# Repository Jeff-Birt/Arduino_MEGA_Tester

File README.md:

# Arduino_MEGA_Tester
This project started out as a way to learn about vintage DRAM chips by building an Arduino based tester. Yes, similar projects exist but part of the fun comes from learning to do it yourself.

After getting the testing of 4164 and 41256 DRAMs working someone asked about testing 4116 DRAMs which require three supply voltages and have the nasty tendency to short the rails together when they fail. This required adding some TVS diode arrays to clamp the I/O to 5V/GND and using some small encapsulated DC-DC converters also made sense.

I started with an Arduino Mega as I had one handy, adn also ported it to the Uno, Micro, and Nano. I designed a PCB around the Micro as well. After using the Mega to build an RCA 1802 tester it ocurred to me that by going back to the Mega with its numerous I/O and larger code space, that I could build a more universal tester.

So, after a 6 month hiatus on the project I picked it up again, moved back to the Mega 2560 and designed a 'Mega Tester' shield for it. The shield accepts 'PODs' which is a daughter board customized for a particular range of ICs. For example the 'DRAM Tester POD' which is for 4116, 4164, 41256 and 41464 DRAMs.

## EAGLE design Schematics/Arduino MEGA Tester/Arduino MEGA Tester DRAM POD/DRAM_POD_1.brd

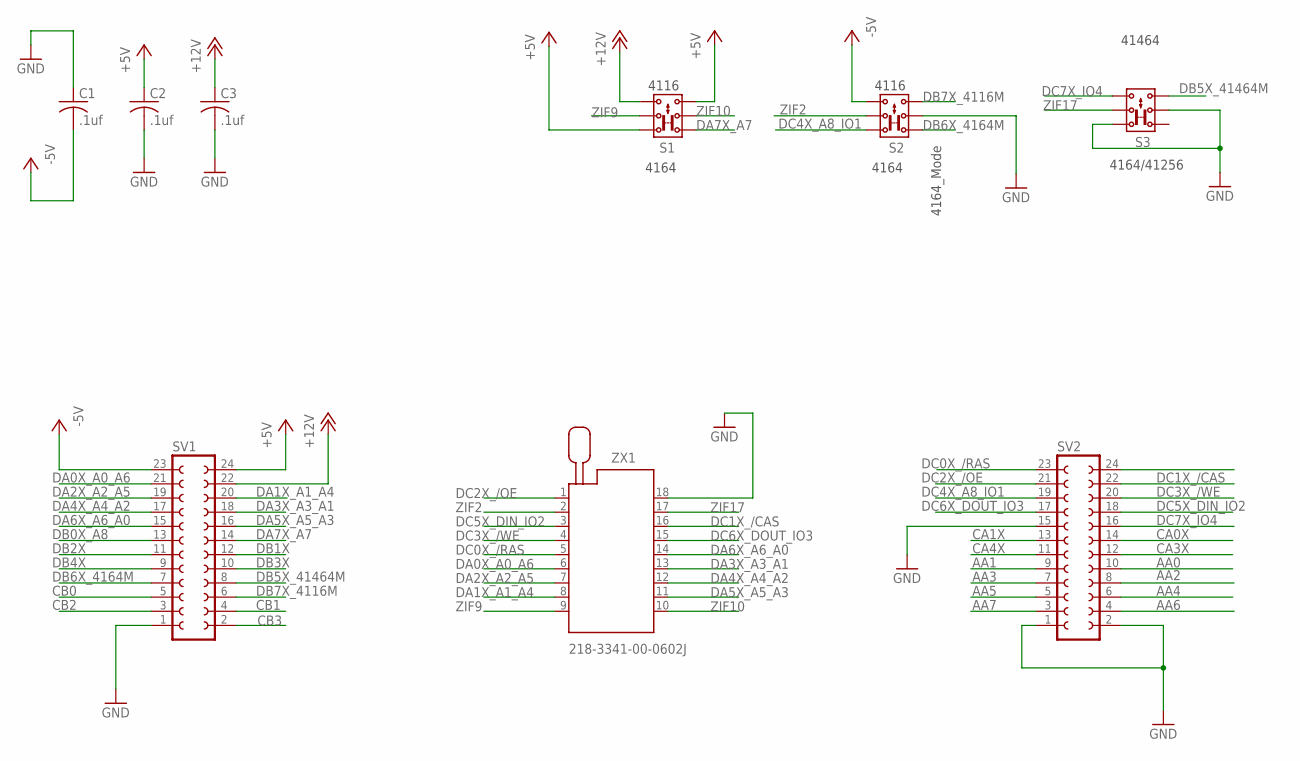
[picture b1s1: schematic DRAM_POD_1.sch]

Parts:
C1, C2, C3: .1uf; C025-024X044
S1, S2, S3: 2P2T
SV1, SV2: FE12-2
ZX1: 218-3341-00-0602J

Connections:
+5V: C2.1, S1.1.1, S1.3.2, SV1.24
+12V: C3.1, S1.3.1, SV1.22
-5V: C1.2, S2.3.1, SV1.23
AA0: SV2.10
AA1: SV2.9
AA2: SV2.8
AA3: SV2.7
AA4: SV2.6
AA5: SV2.5
AA6: SV2.4
AA7: SV2.3
CA0X: SV2.14
CA1X: SV2.13
CA3X: SV2.12
CA4X: SV2.11
CB0: SV1.5
CB1: SV1.4
CB2: SV1.3
CB3: SV1.2
DA0X_A0_A6: SV1.21, ZX1.6
DA1X_A1_A4: SV1.20, ZX1.8
DA2X_A2_A5: SV1.19, ZX1.7
DA3X_A3_A1: SV1.18, ZX1.13
DA4X_A4_A2: SV1.17, ZX1.12
DA5X_A5_A3: SV1.16, ZX1.11
DA6X_A6_A0: SV1.15, ZX1.14
DA7X_A7: S1.1.2, SV1.14
DB0X_A8: SV1.13
DB1X: SV1.12
DB2X: SV1.11
DB3X: SV1.10
DB4X: SV1.9
DB5X_41464M: S3.3.2, SV1.8
DB6X_4164M: S2.1.2, SV1.7
DB7X_4116M: S2.3.2, SV1.6
DC0X_/RAS: SV2.23, ZX1.5
DC1X_/CAS: SV2.22, ZX1.16
DC2X_/OE: SV2.21, ZX1.1
DC3X_/WE: SV2.20, ZX1.4
DC4X_A8_IO1: S2.1.1, SV2.19
DC5X_DIN_IO2: SV2.18, ZX1.3
DC6X_DOUT_IO3: SV2.17, ZX1.15
DC7X_IO4: S3.3.1, SV2.16
GND: C1.1, C2.2, C3.2, S2.2.2, S3.1.1, S3.2.2, SV1.1, SV2.1, SV2.2, SV2.15, ZX1.18
ZIF2: S2.2.1, ZX1.2
ZIF9: S1.2.1, ZX1.9
ZIF10: S1.2.2, ZX1.10
ZIF17: S3.2.1, ZX1.17

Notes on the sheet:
4164
4116
4164/41256
41464
4164_Mode

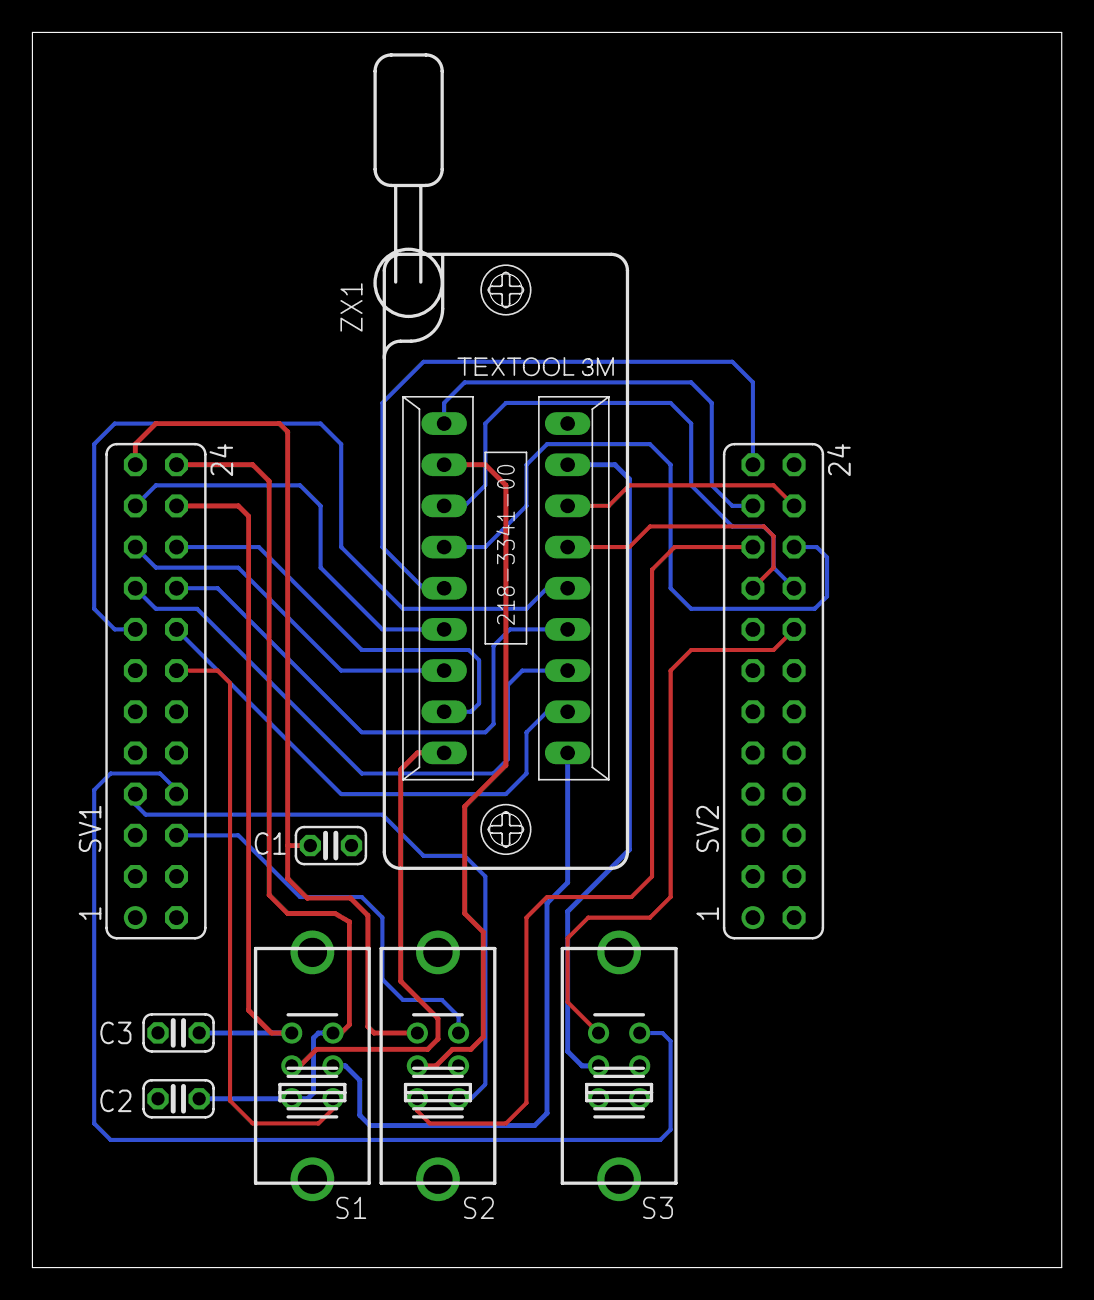
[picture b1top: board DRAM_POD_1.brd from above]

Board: 2 copper layers, 63.5 x 76.2 mm, 9 parts (0 on the bottom side), 27 nets.

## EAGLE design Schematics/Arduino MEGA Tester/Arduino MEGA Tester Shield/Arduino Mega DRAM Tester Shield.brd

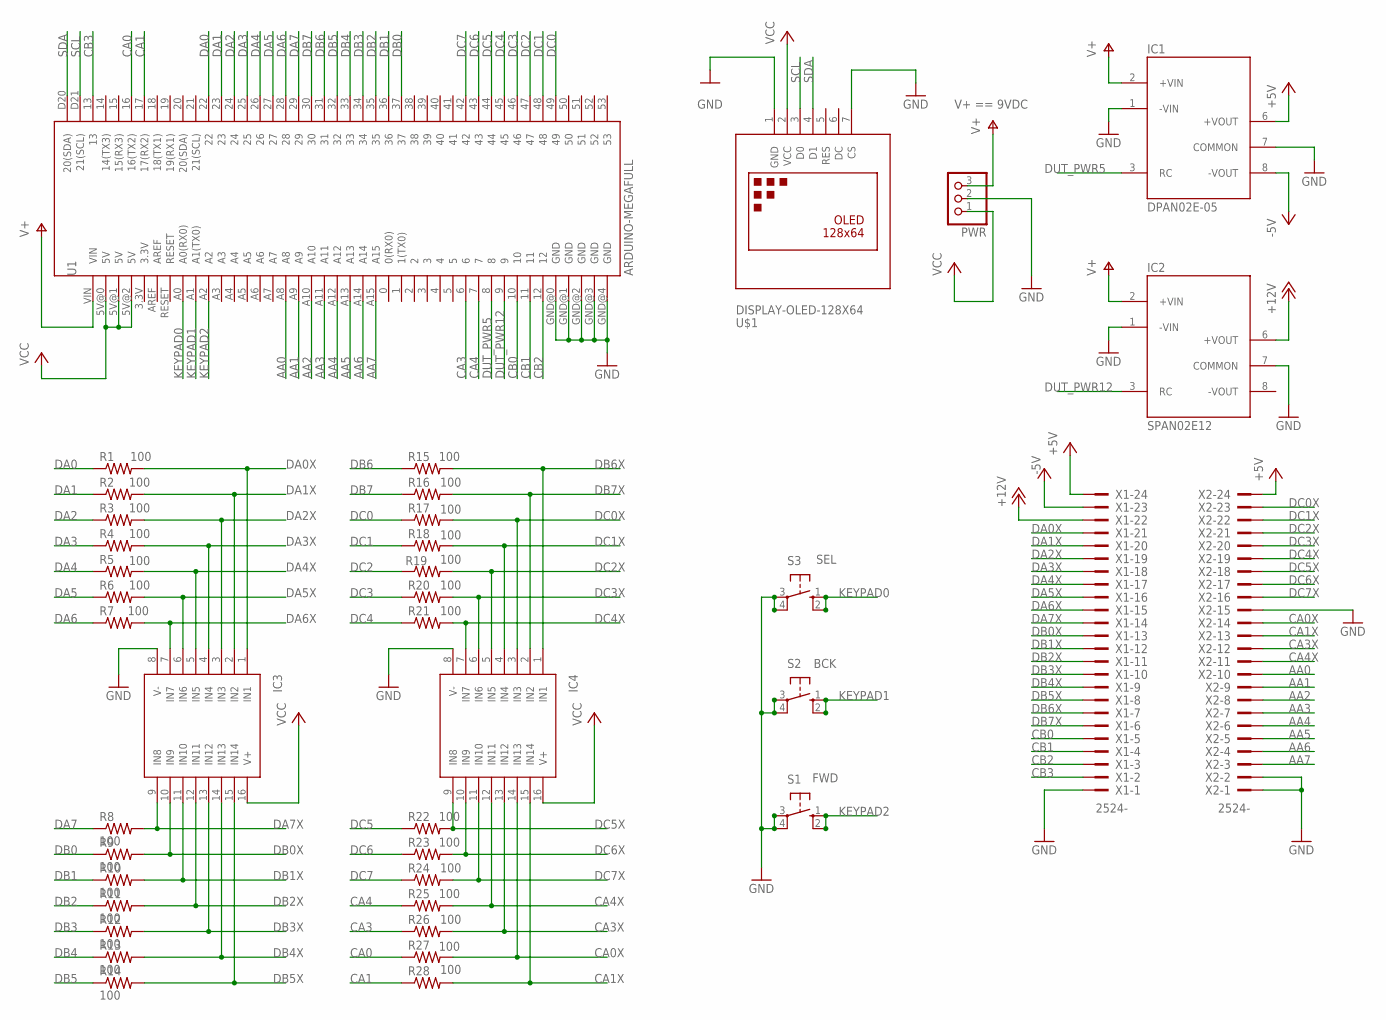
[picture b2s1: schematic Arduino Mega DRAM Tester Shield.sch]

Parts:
IC1: DPAN02E-05; SIP7
IC2: SPAN02E12; SIP7
IC3, IC4: SP720; DIL16
PWR: PINHD-1X3; 1X03
R1, R2, R3, R4, R5, R6, R7, R8, R9, R10, R11, R12, R13, R14, R15, R16, R17, R18, R19, R20, R21, R22, R23, R24, R25, R26, R27, R28: 100; 0204/7
S1: FWD; B3F-10XX
S2: BCK; B3F-10XX
S3: SEL; B3F-10XX
U1: ARDUINO-MEGAFULL; ARDUINO_MEGA
U$1: DISPLAY-OLED-128X64
X1, X2: 2524-; PAK100/2500-24

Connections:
+5V: IC1.6 (+VOUT), X1.24, X2.24
+12V: IC2.6 (+VOUT), X1.22
-5V: IC1.8 (-VOUT), X1.23
AA0: U1.A8, X2.10
AA1: U1.A9, X2.9
AA2: U1.A10, X2.8
AA3: U1.A11, X2.7
AA4: U1.A12, X2.6
AA5: U1.A13, X2.5
AA6: U1.A14, X2.4
AA7: U1.A15, X2.3
CA0: R27.1, U1.16 (16(TX2))
CA0X: IC4.14 (IN13), R27.2, X2.14
CA1: R28.1, U1.17 (17(RX2))
CA1X: IC4.15 (IN14), R28.2, X2.13
CA3: R26.1, U1.6
CA3X: IC4.13 (IN12), R26.2, X2.12
CA4: R25.1, U1.7
CA4X: IC4.12 (IN11), R25.2, X2.11
CB0: U1.10, X1.5
CB1: U1.11, X1.4
CB2: U1.12, X1.3
CB3: U1.13, X1.2
DA0: R1.1, U1.22
DA0X: IC3.1 (IN1), R1.2, X1.21
DA1: R2.1, U1.23
DA1X: IC3.2 (IN2), R2.2, X1.20
DA2: R3.1, U1.24
DA2X: IC3.3 (IN3), R3.2, X1.19
DA3: R4.1, U1.25
DA3X: IC3.4 (IN4), R4.2, X1.18
DA4: R5.1, U1.26
DA4X: IC3.5 (IN5), R5.2, X1.17
DA5: R6.1, U1.27
DA5X: IC3.6 (IN6), R6.2, X1.16
DA6: R7.1, U1.28
DA6X: IC3.7 (IN7), R7.2, X1.15
DA7: R8.1, U1.29
DA7X: IC3.9 (IN8), R8.2, X1.14
DB0: R9.1, U1.37
DB0X: IC3.10 (IN9), R9.2, X1.13
DB1: R10.1, U1.36
DB1X: IC3.11 (IN10), R10.2, X1.12
DB2: R11.1, U1.35
DB2X: IC3.12 (IN11), R11.2, X1.11
DB3: R12.1, U1.34
DB3X: IC3.13 (IN12), R12.2, X1.10
DB4: R13.1, U1.33
DB4X: IC3.14 (IN13), R13.2, X1.9
DB5: R14.1, U1.32
DB5X: IC3.15 (IN14), R14.2, X1.8
DB6: R15.1, U1.31
DB6X: IC4.1 (IN1), R15.2, X1.7
DB7: R16.1, U1.30
DB7X: IC4.2 (IN2), R16.2, X1.6
DC0: R17.1, U1.49
DC0X: IC4.3 (IN3), R17.2, X2.23
DC1: R18.1, U1.48
DC1X: IC4.4 (IN4), R18.2, X2.22
DC2: R19.1, U1.47
DC2X: IC4.5 (IN5), R19.2, X2.21
DC3: R20.1, U1.46
DC3X: IC4.6 (IN6), R20.2, X2.20
DC4: R21.1, U1.45
DC4X: IC4.7 (IN7), R21.2, X2.19
DC5: R22.1, U1.44
DC5X: IC4.9 (IN8), R22.2, X2.18
DC6: R23.1, U1.43
DC6X: IC4.10 (IN9), R23.2, X2.17
DC7: R24.1, U1.42
DC7X: IC4.11 (IN10), R24.2, X2.16
DUT_PWR5: IC1.3 (RC), U1.8
DUT_PWR12: IC2.3 (RC), U1.9
GND: IC1.1 (-VIN), IC1.7 (COMMON), IC2.1 (-VIN), IC2.7 (COMMON), IC3.8 (V-), IC4.8 (V-), PWR.2, S1.3, S1.4 (P1), S2.3, S2.4 (P1), S3.3, S3.4 (P1), U1.GND@0 (GND), U1.GND@1 (GND), U1.GND@2 (GND), U1.GND@3 (GND), U1.GND@4 (GND), U$1.1 (GND), U$1.7 (CS), X1.1, X2.1, X2.2, X2.15
KEYPAD0: S3.1 (S), S3.2 (S1), U1.A0 (A0(RX0))
KEYPAD1: S2.1 (S), S2.2 (S1), U1.A1 (A1(TX0))
KEYPAD2: S1.1 (S), S1.2 (S1), U1.A2
SCL: U1.D21 (21(SCL)), U$1.3 (D0)
SDA: U1.D20 (20(SDA)), U$1.4 (D1)
V+: IC1.2 (+VIN), IC2.2 (+VIN), PWR.3, U1.VIN
VCC: IC3.16 (V+), IC4.16 (V+), PWR.1, U1.5V@0 (5V), U1.5V@1 (5V), U1.5V@2 (5V), U$1.2 (VCC)

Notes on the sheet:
V+ == 9VDC

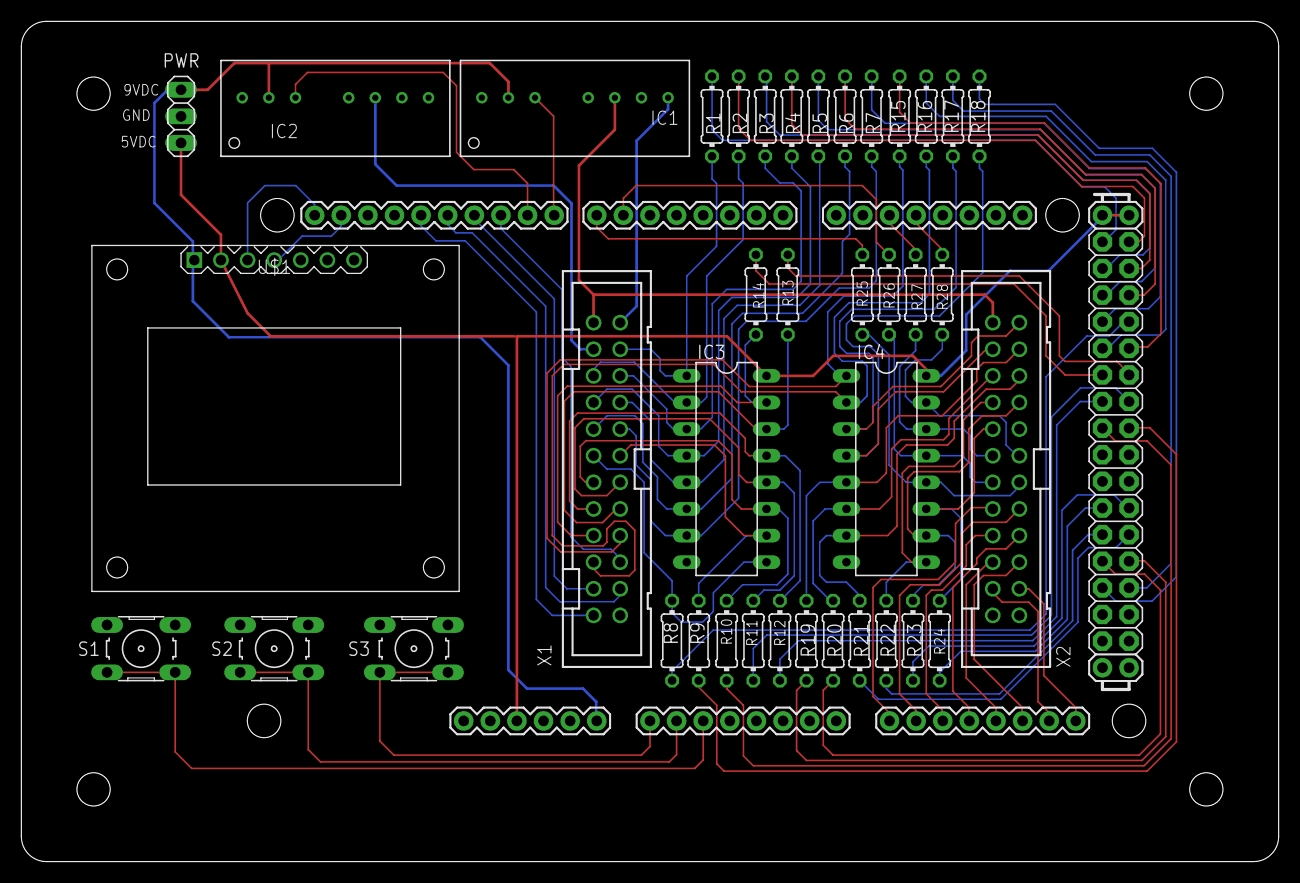
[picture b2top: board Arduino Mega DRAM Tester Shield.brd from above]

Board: 2 copper layers, 120.0 x 80.2 mm, 40 parts (0 on the bottom side), 81 nets.

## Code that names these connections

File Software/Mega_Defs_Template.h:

#pragma once

//PORTA bit           Ard Prt Pin 
#define DA0TODA7  0xFF
//	DA0				      PA0 #22 
//  DA1                   PA1 #23
//  DA2                   PA2 #24
//  DA3                   PA3 #25
//  DA4                   PA4 #26
//  DA5                   PA5 #27
//  DA6                   PA6 #28
//  DA7                   PA7 #29  

//PORTB bit           Ard Prt Pin 
#define CB0T0CB6  0xF7 
//	CB0					  PB0 #53 
//  CB1                   PB1 #52
//  CB2                   PB2 #51
//  CB3                   PB3 #50
//  CB4                   PB4 #10
//  CB5                   PB5 #11
//  CB6                   PB6 #12
//                        PB7 #13  

// PORTC bits         Ard Prt Pin
#define DB0T0DB6  0xFF 
//	DB0					  PC0 #37
//	DB1				      PC1 #36
//	DB2				      PC2 #35
//	DB3				      PC3 #34
//	DB4				      PC4 #33
//	DB5				      PC5 #32  
//  DB6                   PC6 #31
//	DB7			          PC7 #30

// PORTD bits       Ard Prt Pin
#define DISP      0xFF 
//	SCL					  PD0 #21
//	SDA				      PD1 #20
//					      PD2 
//					      PD3 
//					      PD4
//					      PD5  
//                        PD6
//				          PD7

// PORTF bits       Ard Prt Pin
#define UI        0xFF 
//	KEYPAD0				  PF0 #A0
//	KEYPAD1				  PF1 #A1
//	KEYPAD2				  PF2 #A2
//	    				  PF3 #A3
//					      PF4 #A4
//					      PF5 #A5
//                        PF6 #A6
//				          PF7 #A7

// PORTH bits        Ard Prt Pin
#define CC0TOCC1   0xFF 
//	CC0					  PH0 16
//	CC1				      PH1 17
//					      PH2 
//	     				  PH3 
//					      PH4
//	DUT_PWR5		      PH5 8
//  DUT_PWR12             PH6 9
//				          PH7

// PORTJ bits        Ard Prt Pin
#define CA0TOCA1   0xFF 
//	CA0					  PJ0 15
//	CA2				      PJ1 14
//					      PJ2 
//	     				  PJ3 
//					      PJ4
//					      PJ5 
//			              PJ6 
//				          PJ7

// PORTK bits         Ard Prt Pin
#define AA0TOAA7    0xFF 
//	AA0					  PK0 #A8
//	AA1				      PK1 #A9
//	AA2				      PK2 #A10
//	AA3    				  PK3 #A11
//	AA4				      PK4 #A12
//	AA5     		      PK5 #A13
//  AA6                   PK6 #A14
//	AA7 		          PK7 #A15

// PORTL bits         Ard Prt Pin
#define DC0TODC7    0xFF 
//	DC0					  PK0 #49
//	DC1				      PK1 #48
//	DC2				      PK2 #47
//	DC3    				  PK3 #46
//	DC4				      PK4 #45
//	DC5     		      PK5 #44
//  DC6                   PK6 #43
//	DC7 		          PK7 #42

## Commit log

2020-08-19 Initial commit of Arduino MEGA Tester
2020-08-19 Initial commit take 2
2020-08-24 Moved a few I/O around. Added some pin mapping files. Adjusted OLED position.

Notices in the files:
parts and their libraries:
SparkFun-Boards: Licensing: CC v3.0 Share-Alike You are welcome to use this library for commercial purposes.
